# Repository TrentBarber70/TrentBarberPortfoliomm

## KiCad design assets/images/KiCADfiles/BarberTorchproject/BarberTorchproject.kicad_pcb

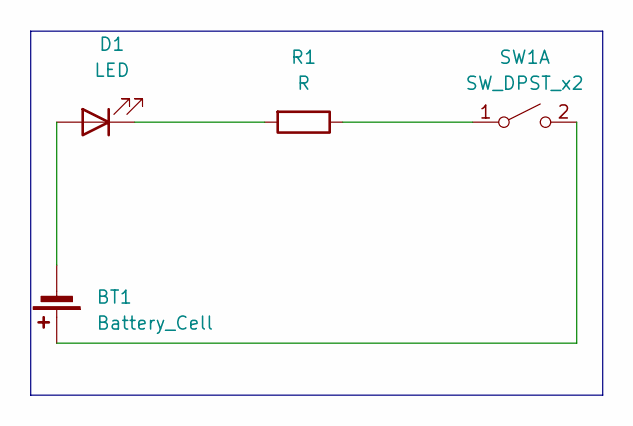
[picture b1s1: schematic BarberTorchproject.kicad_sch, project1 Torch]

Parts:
BT1: Battery_Cell; BatteryHolder_Keystone_1058_1x2032
D1: LED; LED_D5.0mm
R1: R; R_Axial_DIN0207_L6.3mm_D2.5mm_P7.62mm_Horizontal
SW1: SW_DPST_x2; SW_PUSH_6mm

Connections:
unnamed: BT1.1 (+), SW1.2 (B)
unnamed: BT1.2 (-), D1.2 (A)
unnamed: D1.1 (K), R1.2
unnamed: R1.1, SW1.1 (A)

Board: 2 copper layers, 4 parts (0 on the bottom side), 4 nets, no tracks yet.

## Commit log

2025-10-17 picture
2025-10-21 working on portfolio
    added small notes
2025-10-23 Pictures
    added pictures from computer
2025-10-31 pictures and text
2025-11-02 summary of PCB
2025-11-02 pictures for workflow
2025-11-02 Add files via upload
    Resistor practice G-code
2025-11-04 markdown
2025-11-04 markdown stuff
2025-11-04 removed time from posts
    it works now
2025-11-04 changed names
2025-11-20 added the Kicad files for the PCB board
2025-11-20 Summary and Files
2025-11-20 files
2025-12-11 moved files
2025-12-17 added images
2025-12-17 added journals
2025-12-17 Date Changes
2025-12-17 Edits to Post
2025-12-17 images for topograpghy workflow
2025-12-17 Added Topography post
2025-12-17 Final project updates
2025-12-18 updates to journals
2025-12-18 Changes to posts
2025-12-18 Edits to posts
2025-12-18 fixed images
2025-12-18 edits to dates
2025-12-18 Changes to titles
2026-01-04 updates to page
2026-01-04 Updates to pages
2026-01-04 Updated tags
2026-01-04 post changes
2026-01-04 label changes
2026-01-04 items included
2026-01-04 Bullet lists
2026-01-05 Videos added
2026-01-05 video formatting
2026-01-05 Changed downloads
2026-01-05 Edits to summary
2026-01-05 file links
    added file links to the topography page and made edits to final project page.
2026-01-05 journaling
2026-01-05 added Gerber files
2026-01-06 Journal for 1-6-2026
2026-01-06 Changed date
2026-01-08 Journal 1-7-26
2026-01-08 journal 1-8-2026
2026-01-12 Rename 2026-12-01.md to 2026-12-01-post-journal.md
2026-01-12 Rename 2026-12-01-post-journal.md to 2026-01-12-post-journal.md
2026-01-12 Gantt chart
2026-01-21 New Journals for 1-14__1-20
2026-01-21 Updates to posts
2026-03-08 February-March posts
2026-03-08 Checkpoint post 2
